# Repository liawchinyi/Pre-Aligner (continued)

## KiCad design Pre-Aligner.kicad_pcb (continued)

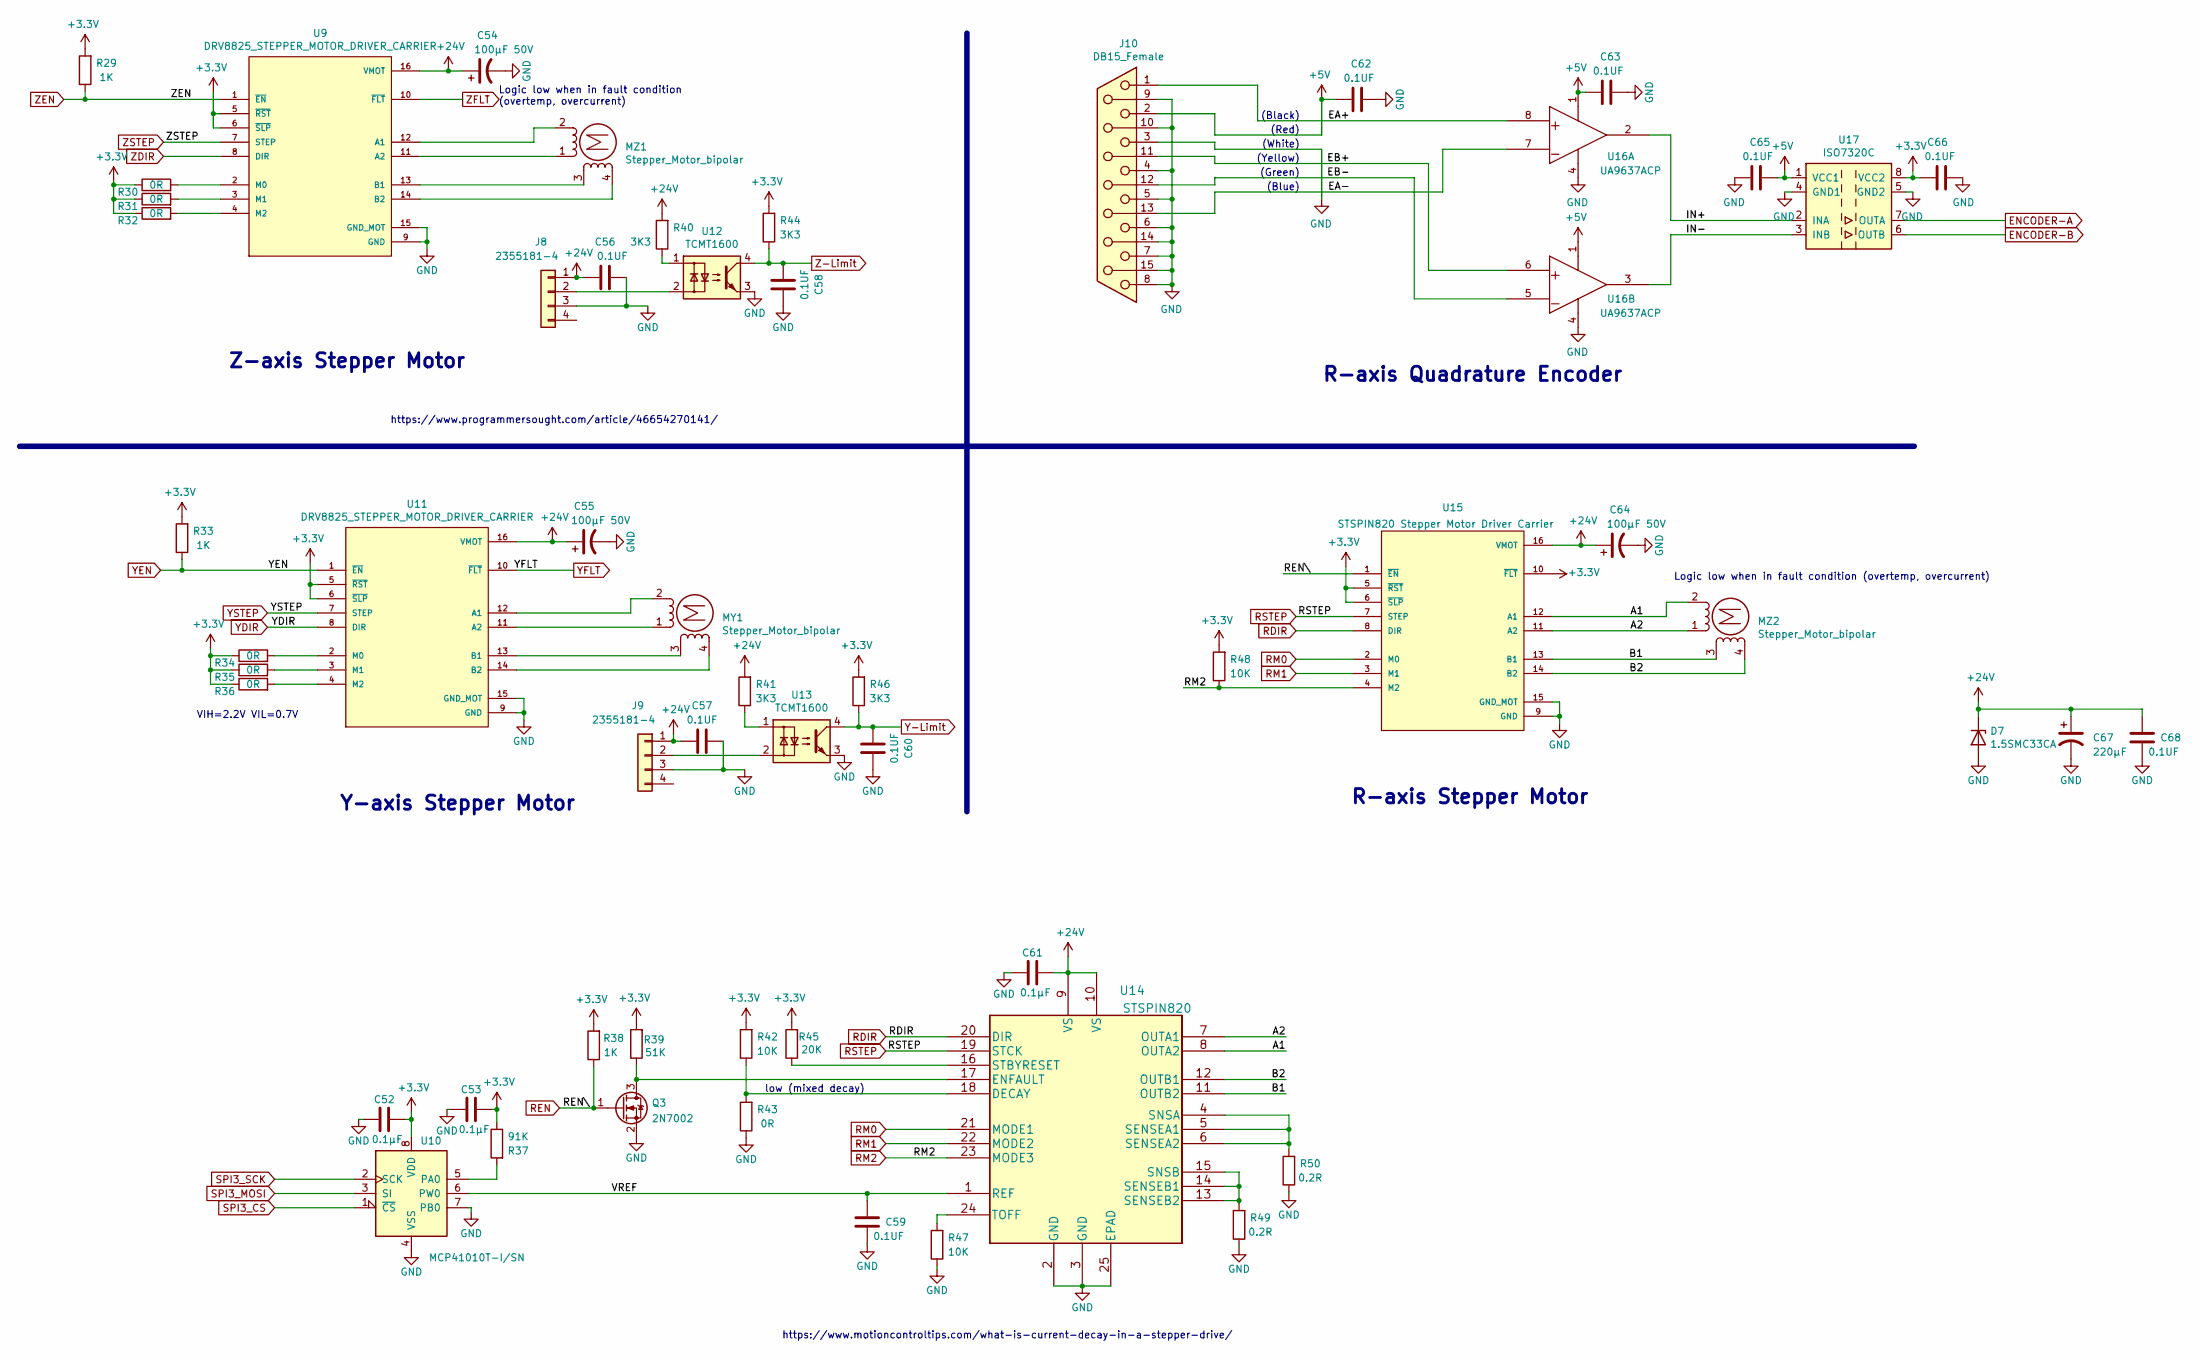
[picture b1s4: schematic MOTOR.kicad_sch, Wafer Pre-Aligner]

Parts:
C52, C53, C61: 0.1µF; C_0402_1005Metric; Manufacturer_Part_Number GRM155R71C104KA88J
C54, C55, C64: 100µF 50V; CP_Elec_10x10; Manufacturer_Part_Number EEE-FC1H101P
C56, C57, C58, C59, C60, C62, C63, C65, C66, C68: 0.1UF; C_0603_1608Metric; Manufacturer_Part_Number C0603C104M5RACTU
C67: 220µF; CP_Elec_10x10.5; Manufacturer_Part_Number UWT1H221MNL1GS
D7: 1.5SMC33CA; D_SMC; Manufacturer_Part_Number 1.5SMC33CA
J8, J9: 2355181-4; TE_440054-4; Manufacturer_Part_Number 2355181-4
J10: DB15_Female; DSUB-15-HD_Female_Vertical_P2.29x1.98mm_MountingHoles; Manufacturer_Part_Number 10090929-S154XLF
MY1: Stepper_Motor_bipolar; JST_EH_B4B-EH-A_1x04_P2.50mm_Vertical; Manufacturer_Part_Number 640456-4
MZ1, MZ2: Stepper_Motor_bipolar; JST_EH_B4B-EH-A_1x04_P2.50mm_Vertical; Manufacturer_Part_Number 640456-4
Q3: 2N7002; SOT-23; Manufacturer_Part_Number 2N7002
R29, R33, R38: 1K; R_0603_1608Metric; Manufacturer_Part_Number RC0603JR-071KL
R30, R31, R32, R34, R35, R36: 0R; R_0603_1608Metric; Manufacturer_Part_Number RMCF0603ZT0R00
R37: 91K; R_0603_1608Metric; Manufacturer_Part_Number ERJ-3GEYJ913V
R39: 51K; R_0603_1608Metric; Manufacturer_Part_Number RT0603FRE0751KL
R40, R41, R44, R46: 3K3; R_0603_1608Metric; Manufacturer_Part_Number ERJ-3GEYJ332V
R42, R47, R48: 10K; R_0603_1608Metric; Manufacturer_Part_Number ERJ-3GEYJ103V
R43: 0R; R_0603_1608Metric; Manufacturer_Part_Number CR0603AJ/-000EAS
R45: 20K; R_0603_1608Metric; Manufacturer_Part_Number ERA-3AEB203V
R49, R50: 0.2R; RES_ERJB1CFR036U; Manufacturer_Part_Number ERJ-D1CFR200U
U9, U11: DRV8825_STEPPER_MOTOR_DRIVER_CARRIER; Manufacturer_Part_Number DRV8825
U10: MCP41010T-I/SN; SOIC-8-1EP_3.9x4.9mm_P1.27mm_EP2.29x3mm; Manufacturer_Part_Number MCP41010T-I/SN
U12, U13: TCMT1600; SOP-4_4.4x2.6mm_P1.27mm; Manufacturer_Part_Number TCMT1600
U14: STSPIN820; QFN_SPIN820_STM; Manufacturer_Part_Number STSPIN820
U15: STSPIN820 Stepper Motor Driver Carrier; SPSPIN820_STEPPER_MOTOR_DRIVER_CARRIER; Manufacturer_Part_Number STSPIN820
U16: UA9637ACP; DIP-8_W7.62mm; Manufacturer_Part_Number UA9637ACDR
U17: ISO7320C; SOIC-8_3.9x4.9mm_P1.27mm; Manufacturer_Part_Number ISO7320CQDRQ1

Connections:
24V: C54.1, C55.1, C56.1, C57.1, C61.2, C64.1, C67.1, C68.2, D7.1 (K), J8.1, J9.1, R40.2, R41.2, U9.16 (VMOT), U11.16 (VMOT), U14.9 (VS), U14.10 (VS), U15.16 (VMOT); also elsewhere on the board
+5V: C62.2, C63.2, C65.1, J10.2, U16.1 (VCC), U17.1 (VCC1); also elsewhere on the board
/MOTOR/A1: MZ2.2 (-), U14.8 (OUTA2), U15.12 (A1)
/MOTOR/A2: MZ2.1, U14.7 (OUTA1), U15.11 (A2)
/MOTOR/B1: MZ2.3, U14.11 (OUTB2), U15.13 (B1)
/MOTOR/B2: MZ2.4, U14.12 (OUTB1), U15.14 (B2)
/MOTOR/EA+: J10.1, U16.8 (IN+)
/MOTOR/EA-: J10.13, U16.7 (IN-)
/MOTOR/EB+: J10.11 (P111), U16.6 (IN+)
/MOTOR/EB-: J10.12, U16.5 (IN-)
/MOTOR/IN+: U16.2 (OUT), U17.2 (INA)
/MOTOR/IN-: U16.3 (OUT), U17.3 (INB)
/MOTOR/VREF: C59.2, U10.6 (PW0), U14.1 (REF)
ENCODER-A: U17.7 (OUTA); also elsewhere on the board
ENCODER-B: U17.6 (OUTB); also elsewhere on the board
GND: C52.1, C53.1, C54.2, C55.2, C56.2, C57.2, C58.2, C59.1, C60.2, C61.1, C62.1, C63.1, C64.2, C65.2, C66.2, C67.2, C68.1, D7.2 (A), J8.3, J9.3, J10.3, J10.4, J10.5, J10.6, J10.7, J10.8, J10.9, J10.10, J10.14, J10.15, Q3.2 (S), R43.1, R47.1, R49.1, R50.1, U9.9 (GND), U9.15 (GND_MOT), U10.4 (VSS), U10.7 (PB0), U11.9 (GND), U11.15 (GND_MOT), U12.3, U13.3, U14.2 (GND), U14.3 (GND), U14.25 (EPAD), U15.9 (GND), U15.15 (GND_MOT), U16.4 (GND), U17.4 (GND1), U17.5 (GND2); also elsewhere on the board
unnamed: J8.2, U12.2
unnamed: J9.2, U13.2
unnamed: MY1.1, U11.11 (A2)
unnamed: MY1.2 (-), U11.12 (A1)
unnamed: MY1.3, U11.13 (B1)
unnamed: MY1.4, U11.14 (B2)
unnamed: MZ1.1, U9.11 (A2)
unnamed: MZ1.2 (-), U9.12 (A1)
unnamed: MZ1.3, U9.13 (B1)
unnamed: MZ1.4, U9.14 (B2)
unnamed: Q3.3 (D), R39.1, U14.17 (ENFAULT)
unnamed: R30.2, U9.2 (M0)
unnamed: R31.2, U9.3 (M1)
unnamed: R32.2, U9.4 (M2)
unnamed: R34.2, U11.2 (M0)
unnamed: R35.2, U11.3 (M1)
unnamed: R36.2, U11.4 (M2)
unnamed: R37.2, U10.5 (PA0)
unnamed: R40.1, U12.1
unnamed: R41.1, U13.1
unnamed: R42.1, R43.2, U14.18 (DECAY)
unnamed: R45.1, U14.16 (STBYRESET)
unnamed: R47.2, U14.24 (TOFF)
unnamed: R49.2, U14.13 (SENSEB2), U14.14 (SENSEB1), U14.15 (SNSB)
unnamed: R50.2, U14.4 (SNSA), U14.5 (SENSEA1), U14.6 (SENSEA2)
RDIR: U14.20 (DIR), U15.8 (DIR); also elsewhere on the board
REN: Q3.1 (G), R38.1, U15.1 (~EN); also elsewhere on the board
RM0: U14.21 (MODE1), U15.2 (M0); also elsewhere on the board
RM1: U14.22 (MODE2), U15.3 (M1); also elsewhere on the board
RM2: R48.1, U14.23 (MODE3), U15.4 (M2)
RSTEP: U14.19 (STCK), U15.7 (STEP); also elsewhere on the board
SPI3_CS: U10.1 (~CS); also elsewhere on the board
SPI3_MOSI: U10.3 (SI); also elsewhere on the board
SPI3_SCK: U10.2 (SCK); also elsewhere on the board
Y-Limit: C60.1, R46.1, U13.4; also elsewhere on the board
YDIR: U11.8 (DIR); also elsewhere on the board
YEN: R33.1, U11.1 (~EN); also elsewhere on the board
YFLT: U11.10 (~FLT)
YSTEP: U11.7 (STEP); also elsewhere on the board
Z-Limit: C58.1, R44.1, U12.4; also elsewhere on the board
ZDIR: U9.8 (DIR); also elsewhere on the board
ZEN: R29.1, U9.1 (~EN); also elsewhere on the board
ZFLT: U9.10 (~FLT); also elsewhere on the board
ZSTEP: U9.7 (STEP); also elsewhere on the board

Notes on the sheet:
Z-axis Stepper Motor
VIH=2.2V VIL=0.7V
Y-axis Stepper Motor
low (mixed decay)
Logic low when in fault condition (overtemp, overcurrent)
(Blue)
https://www.motioncontroltips.com/what-is-current-decay-in-a-stepper-drive/
R-axis Quadrature Encoder
(Red)
(Yellow)
https://www.programmersought.com/article/46654270141/
(Black)
R-axis Stepper Motor
Logic low when in fault condition (overtemp, overcurrent)
(White)
(Green)

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
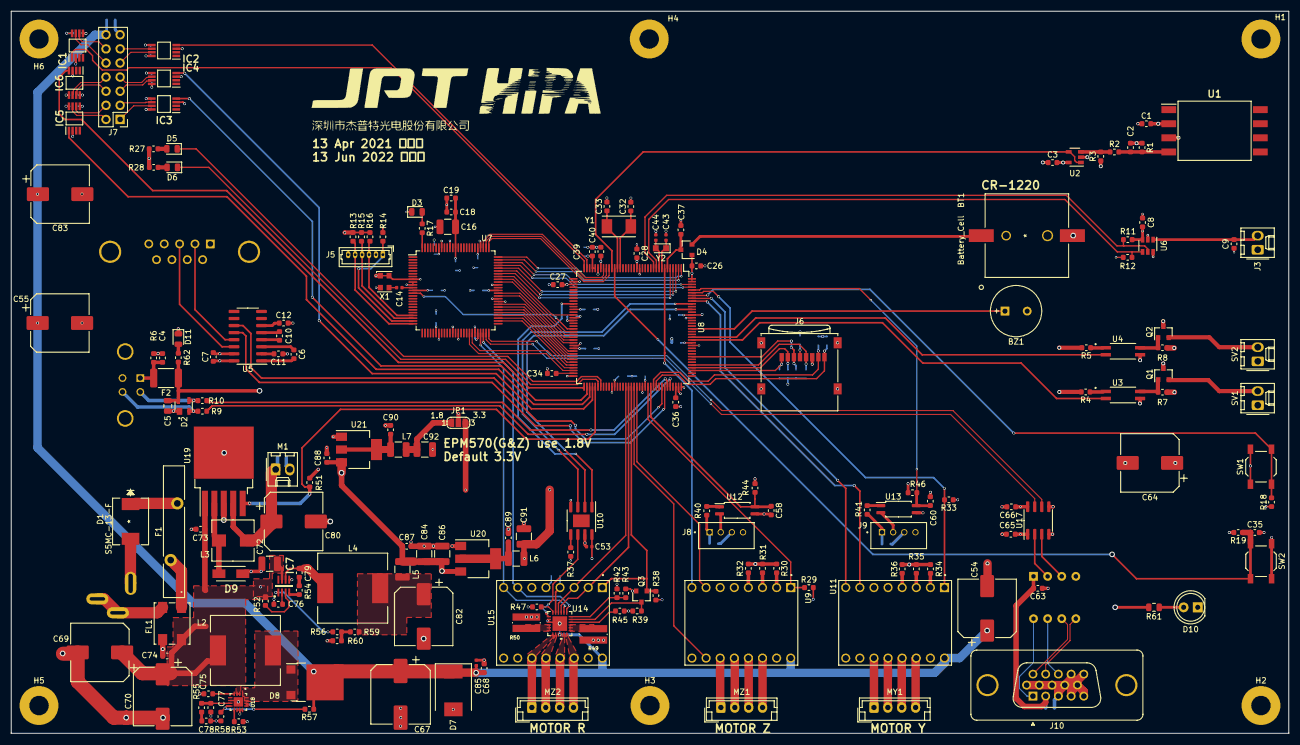
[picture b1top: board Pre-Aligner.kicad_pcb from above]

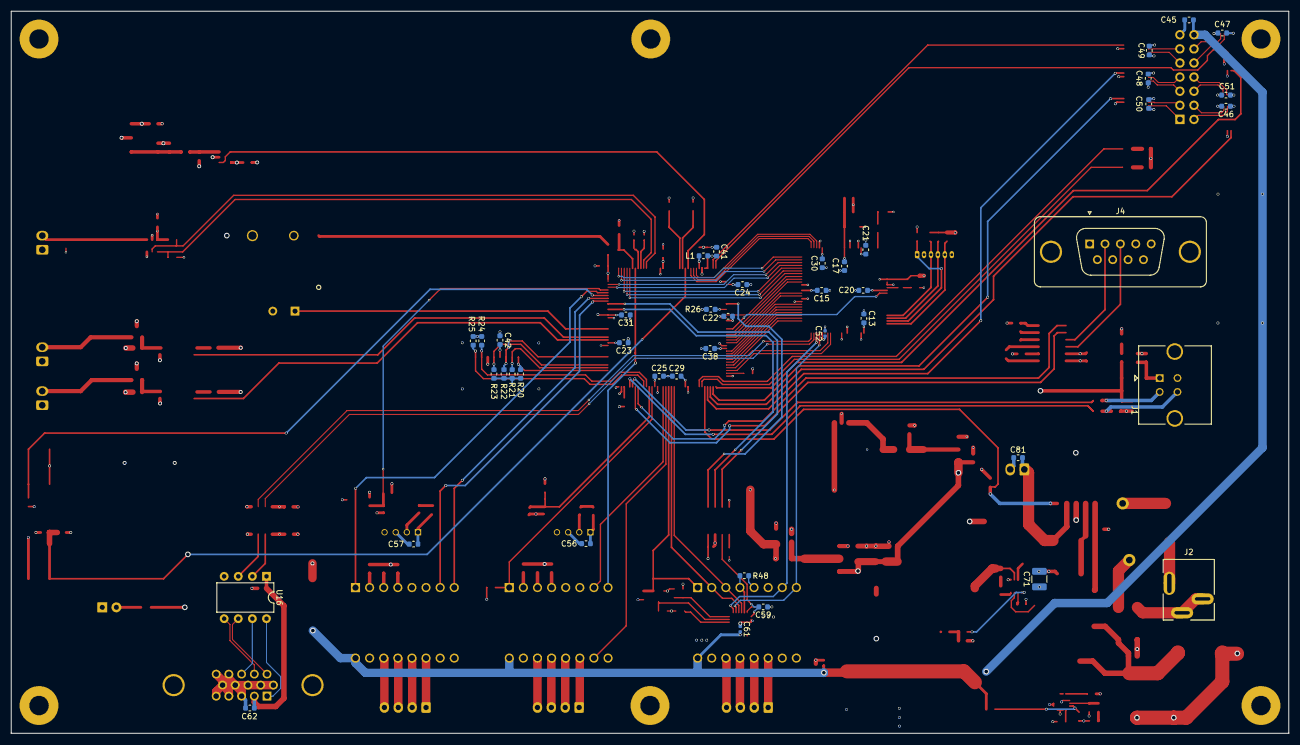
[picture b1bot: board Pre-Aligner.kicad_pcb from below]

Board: 4 copper layers, 230.0 x 130.0 mm, 238 parts (43 on the bottom side), 191 nets.

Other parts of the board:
G1: LOGO; JPT-LOGO
G2: LOGO; HI_PA_3CM

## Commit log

2021-12-30 Initial Upload
